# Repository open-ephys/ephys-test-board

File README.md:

# General purpose, automated electrophysiology test board

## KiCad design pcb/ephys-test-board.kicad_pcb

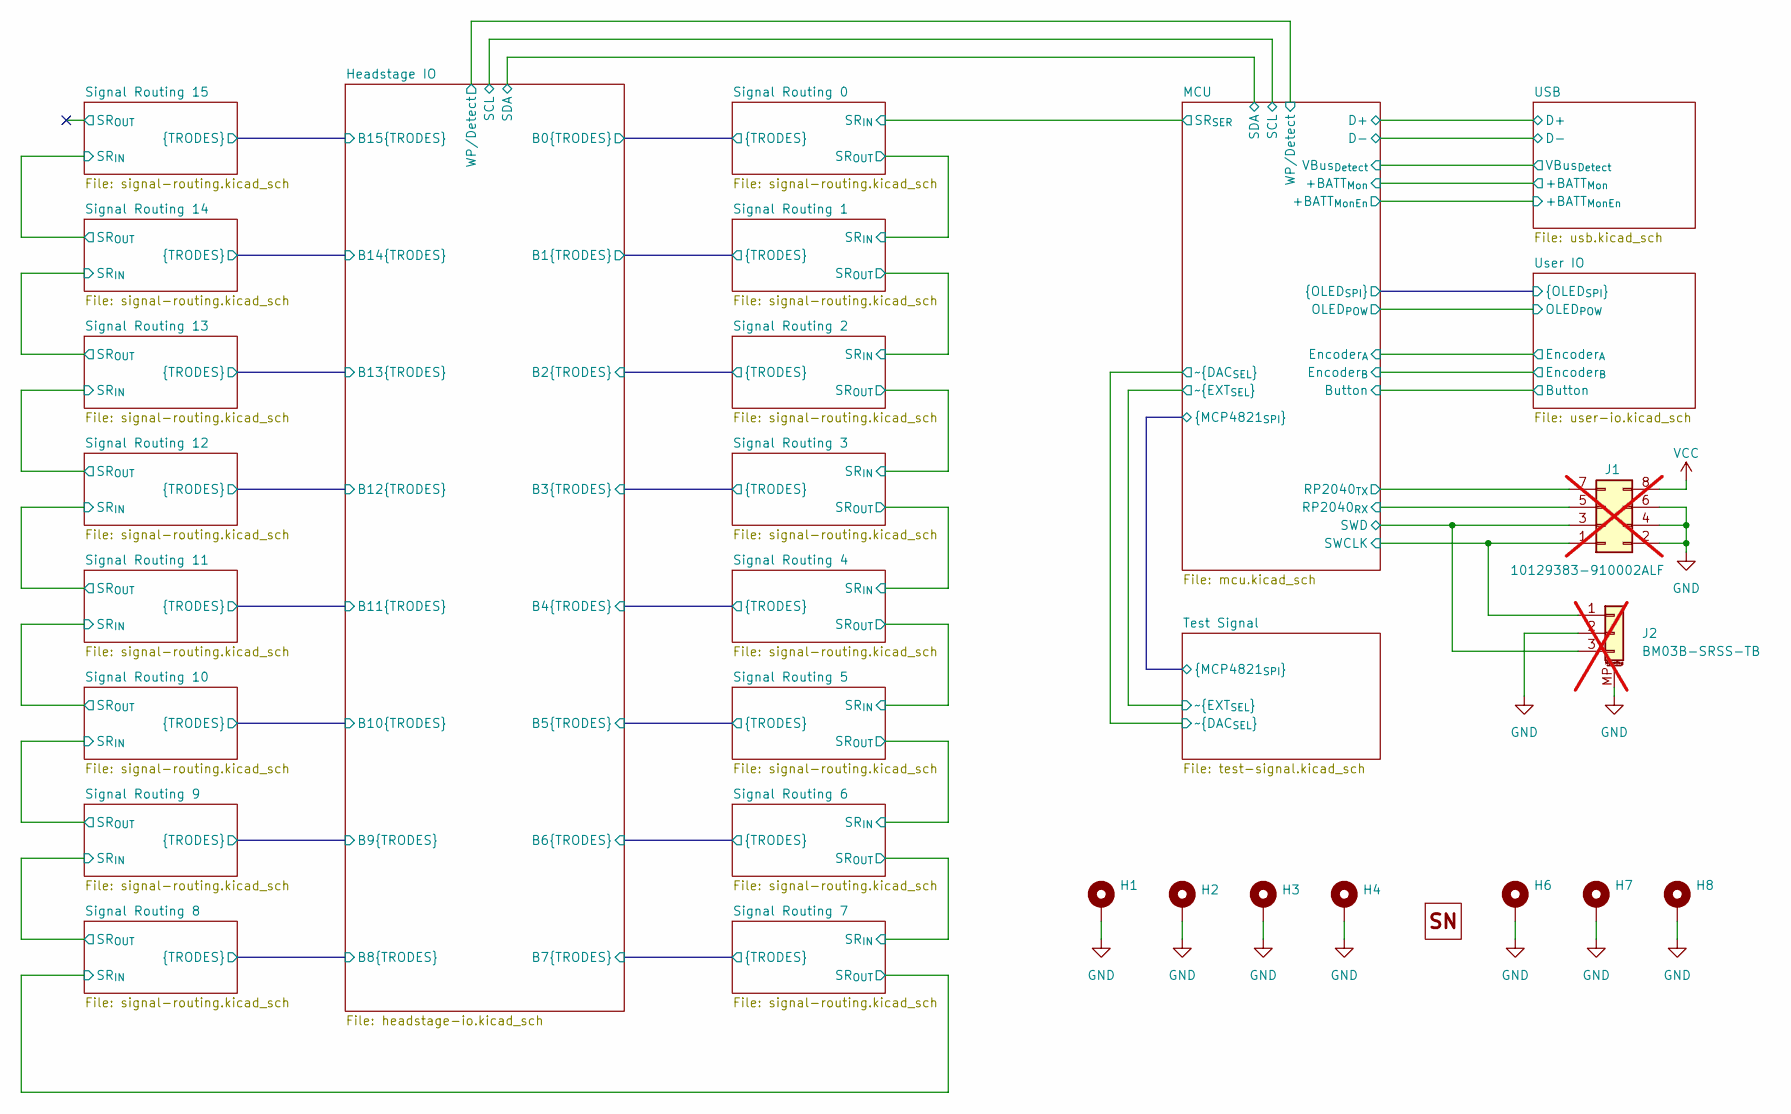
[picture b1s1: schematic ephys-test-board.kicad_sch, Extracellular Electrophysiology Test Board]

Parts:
H1, H2, H3, H4, H6, H7, H8: MountingHole_3.2mm_M3_ISO7380_Pad
H5: OEPS_SN-STICKER-8x20mm
J1: 10129383-910002ALF; PinHeader_2x04_P2.54mm_Vertical_SMD; MPN 10129383-910002ALF; not fitted
J2: BM03B-SRSS-TB; JST_SH_BM03B-SRSS-TB_1x03-1MP_P1.00mm_Vertical; MPN BM03B-SRSS-TB; not fitted

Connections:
/MCU/RP2040_{RX}: J1.5; also elsewhere on the board
/MCU/RP2040_{TX}: J1.7; also elsewhere on the board
/MCU/SWCLK: J1.1, J2.1; also elsewhere on the board
/MCU/SWD: J1.3, J2.3; also elsewhere on the board
GND: H1.1 (1_1), H2.1 (1_1), H3.1 (1_1), H4.1 (1_1), H6.1 (1_1), H7.1 (1_1), H8.1 (1_1), J1.2, J1.4, J1.6, J2.2, J2.MP (MountPin); also elsewhere on the board
VCC: J1.8; also elsewhere on the board

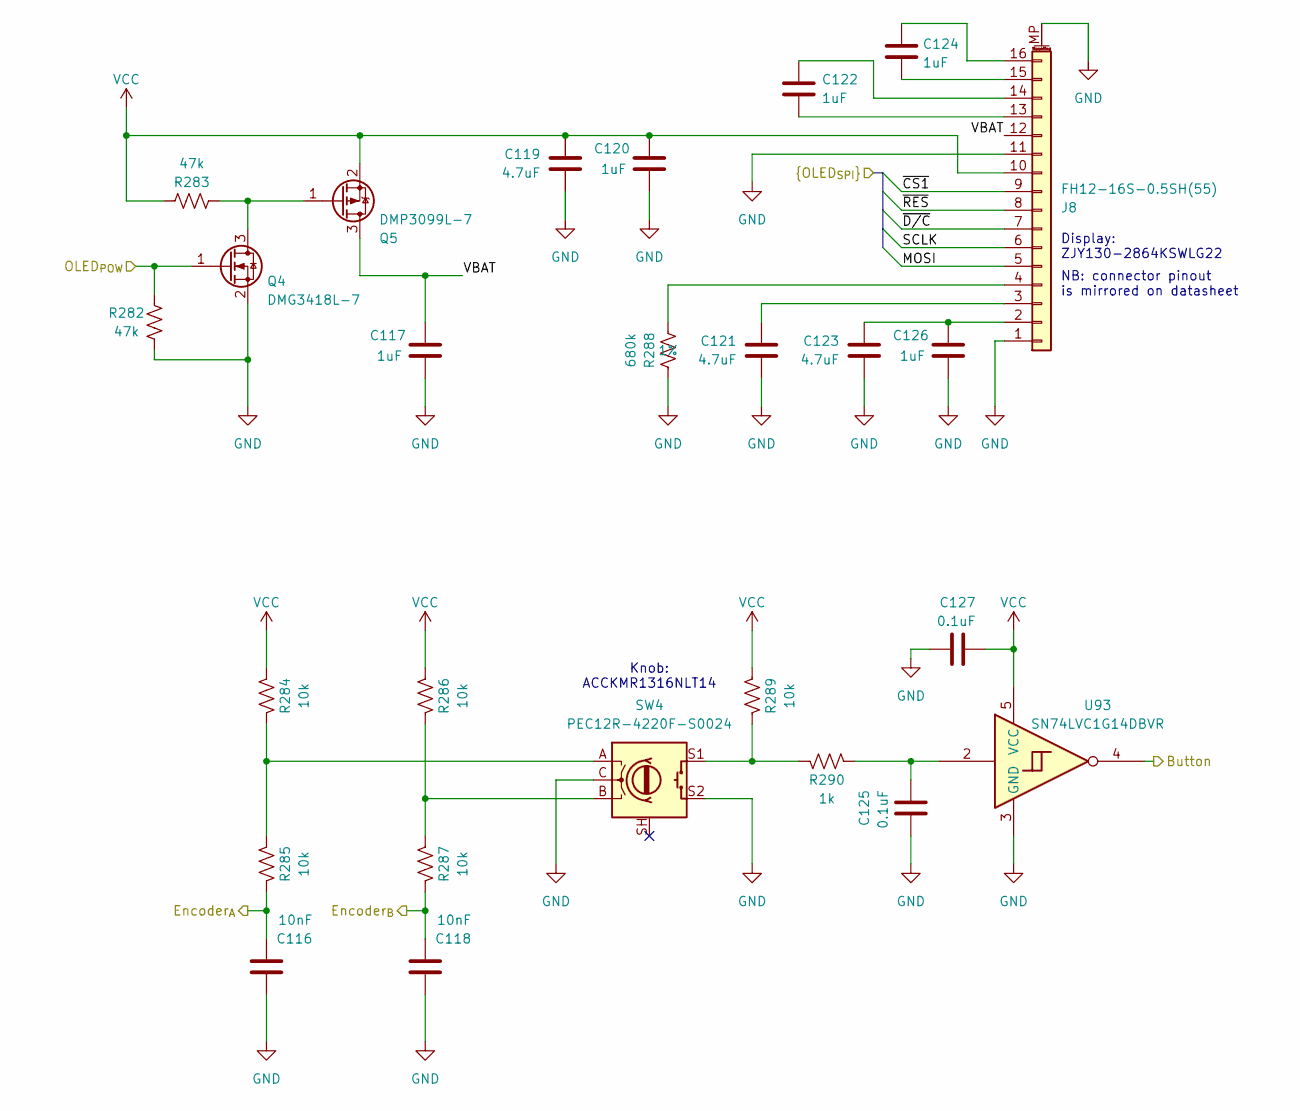
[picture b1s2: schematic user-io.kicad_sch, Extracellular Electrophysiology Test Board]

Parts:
C116, C118: 10nF; C_0402_1005Metric; Voltage 50V; MPN GRM155R71E103KA01D; LCSC C60133
C117, C120, C122, C124, C126: 1uF; C_0603_1608Metric; Voltage 16V; MPN CL10A105KA8NNNC; LCSC C5673
C119, C121, C123: 4.7uF; C_1206_3216Metric; Voltage 16V; MPN CL31B475KOHNNNE; LCSC C51205
C125, C127: 0.1uF; C_0402_1005Metric; Voltage 25V; MPN C1005X7R1E104K050BB; LCSC C105883
J8: FH12-16S-0.5SH(55); Hirose_FH12-16S-0.5SH_1x16-1MP_P0.50mm_Horizontal; MPN FH12-16S-0.5SH(55); LCSC C262665
Q4: DMG3418L-7; SOT-23; MPN DMG3418L-7; LCSC C151026
Q5: DMP3099L-7; SOT-23; MPN DMP3099L-7; LCSC C155244
R282, R283: 47k; R_0402_1005Metric; MPN ERJ-2RKF4702X; LCSC C93943
R284, R285, R286, R287, R289: 10k; R_0402_1005Metric; MPN CRCW040210K0FKED; LCSC C60490
R288: 680k; R_0402_1005Metric; Tolerance 1%; MPN RC0402FR-13680KL; LCSC C2909377
R290: 1k; R_0402_1005Metric; Tolerance 0.1%; MPN RG1005P-102-B-T5; LCSC C2073397
SW4: PEC12R-4220F-S0024; RotaryEncoder_Bourns_Vertical_PEC12R-3x17F-Sxxxx; MPN PEC12R-4220F-S0024; LCSC C18164805
U93: SN74LVC1G14DBVR; SOT-23-5; MPN SN74LVC1G14DBVR; LCSC C7835

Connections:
/MCU/Button: U93.4; also elsewhere on the board
/MCU/Encoder_{A}: C116.1, R285.2; also elsewhere on the board
/MCU/Encoder_{B}: C118.1, R287.2; also elsewhere on the board
/MCU/MOSI: J8.5; also elsewhere on the board
/MCU/OLED_{POW}: Q4.1 (G), R282.1; also elsewhere on the board
/MCU/SCLK: J8.6; also elsewhere on the board
/MCU/~CS1: J8.9; also elsewhere on the board
/MCU/~D/C: J8.7; also elsewhere on the board
/MCU/~RES: J8.8; also elsewhere on the board
/User IO/VBAT: C117.2, J8.12, Q5.3 (D)
GND: C116.2, C117.1, C118.2, C119.2, C120.1, C121.2, C123.2, C125.2, C126.1, C127.2, J8.1, J8.11, J8.MP (MountPin), Q4.2 (S), R282.2, R288.2, SW4.C, SW4.S2, U93.3 (GND); also elsewhere on the board
unnamed: C125.1, R290.2, U93.2
unnamed: C123.1, C126.2, J8.2
unnamed: C121.1, J8.3
unnamed: J8.4, R288.1
unnamed: C122.1, J8.13
unnamed: C122.2, J8.14
unnamed: C124.1, J8.15
unnamed: C124.2, J8.16
unnamed: Q4.3 (D), Q5.1 (G), R283.1
unnamed: R284.2, R285.1, SW4.A
unnamed: R286.2, R287.1, SW4.B
unnamed: R289.2, R290.1, SW4.S1
VCC: C119.1, C120.2, C127.1, J8.10, Q5.2 (S), R283.2, R284.1, R286.1, R289.1, U93.5 (VCC); also elsewhere on the board

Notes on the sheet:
Display: ZJY130-2864KSWLG22
Knob: ACCKMR1316NLT14
NB: connector pinout is mirrored on datasheet

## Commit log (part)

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2024-01-03 Initial commit
    - Add proof of concept signal path verification board
2024-01-08 Started messing around with firmware
    - Messing around with pico-sdk and thinking about how the board will operate.
    - This is just scratch code.
2024-01-29 Add results from signal-path-test board
    - The conclusion is obvious in hind-sight: attenuation must occur after
    analog switches otherwise the small noise of the signal is added to
    the attenuated signal. If attenuation occurs after the switch, this
    still occurs but the lage signal and added noise are _both_ attenuated
    and the noise from the switch is not relevant
2024-01-29 Add initial ephys test board schematic
    - Needs a display to be added
    - Needs concreate part numbers and packages
2024-05-21 Remove battery power option
    - This device needs user IO
    - Battery power means there would need to be a touch screen or wireless
    connection. Too complex.
2024-10-11 Motif is repeated
    - some components are grouped by function
    - components are roughly organized within groups
2024-11-03 Add Cris's instructions for repeating circuit motif
    - Minor edits to markdown
2024-11-08 Manual cleanup of repeated analog input array
    - There was some manual cleanup needed
    - Overall the repeated motif worked very well
2024-11-08 Added user IO and battery
    - Battery provides noise free operation
    - OLED display and rotary encoder are not that hard to use
2024-11-09 Add EEPROM support to headstage interface
    - I2C + Power
2024-11-10 More schematic improvements
    - Add pullups to i2c bus
    - Add test points
    - Ready for initial routing
2024-11-11 Start routing rev. A
2024-11-12 Routing nearly complete
    - Power switch is too tall I think
2024-11-14 Created case
    - Mill aluminum
    - Moved some components for more sensical layout for the user
    - Pending final check, should be ready for initial fab
2024-11-15 Improved manufacturability of case design
    - Quote request sent to PCBWay for this design along with the case
2024-11-15 Update pdf of schematic
    - Additionally, add spice verification of AD5683's
    ability to drive the combined capacitive and
    resistive load presented by the AC coupling
    and attenuation networks
2024-11-19 Fix MCP73831 subcircuit
    - Add decoupling capacitor on Vbat
    - Add more thermal support to layout (solid connection of ground to
    ground plane copper and addition of thermal vias)
2025-01-10 OLED firmware scratch
    - Minimal use of Adafruit graphics libaries
    - Functioned hacked to permit use with Pico SDK
    - translations.h/cpp provides unimplemented hardware translation code
    - Compliles but does nothing currently
    - This is all scratch pad for testing a possible solution for driving
    OLED
2025-01-22 Address several issues found when testing rev. A
    - Add Reset button to back panel
    - Make board smaller
    - Move battery to bottom of device
    - Replace OLED with a more reasonable choice.
    - Etc.
2025-02-06 Change power switch
    - Replace push button with rocker
    - Added some notches to outside of PCB for aligning with enclosure
    - Upgrade to KiCAD 9.0
2025-02-07 Revision B
    - Sent to fab
2025-02-09 Move SW4 closer to PCB edge
    - Also, correct its footprint to 5.8mm actuator length rather than 8.3
    which did not match its part number
2025-02-09 Fix J4 value
    - FH12-16S-0.5SH(55) instead of FH12-24S-0.5SH(55)
2025-02-28 Mirror connections on J4
    - The schematic presented on OLED datasheet was mirrored commpared to
    the connector's pin order. This fixes that.
2025-02-28 Decrease charge indication LED brightness
    - 1k current limiting resistor replaced with 4.7k
2025-03-12 Firmware work
    - Added mode seleciton capabilites
    - Started on channel selection, etc
2025-03-15 Firmware work in progress
    - Knob turns in correct direction
    - Working on incorporating waveform information into waveform generator
2025-03-18 Functional firmware
    - There are some TODOs throughout the code but but this is nearly
    feature complete
    - Spikes waveform maps to sawtooth, that needs to be changed
    - Channel cycling, module eeprom loading, knob hysteresis, and much more
    is all taken care of
2025-03-20 Firmware updates
    - Press button now cycles selection
    - Slow down quadrature PIO state machine to prevent glitching
    - Remove redundant OLED update calls
    - Code cleanup and streamlining
2025-03-20 Reduce test signal attenuation
    - From -60 dbV to -54 dbV
2025-03-20 Add SC0914(13) to Part No. field of RP2040
2025-03-20 Correct max amplitude
    - It was 250 uV but should be 2500 uV
2025-03-21 Case for revision C of PCB
    - Will require some modifications to screen area if its to be
    machinable.
2025-03-21 Add open ephys sheet to pcb design
2025-03-26 Add light pipe part to schematic.
2025-03-29 Address issues with case found during proptyping
    - Add recess for reset button
    - Add 3.5V power managment circuit and simplify on/off switch debounce
    - Increase space in bottom porition of case for thicker battery
    - Remove alignment notches from PCB -- uses features of case instead
2025-04-01 Add silkscreen design for case
    - Also, add recess for sticker on bottom of case
    - Improve case manufacturablity after testing
2025-04-07 Remove signal-path-test-board
    - It has been integrated into the main board
2025-04-07 Add license
2025-04-07 Update gerbers with latest
    - Board Rev -> Rev on silk layer
2025-04-09 Add protention diode to USB input
    - Same part that has been verified on stimjim-hv
2025-04-15 Added OEPS PN.
2025-04-16 Minor edits during BOM review
    - Remove DNP in value fields since a dedicated channel is provided for
    that information
    - Add MP pins to header symbols
    - Update BOM and PDFs
    - New gerbers to connect mount points to headers. No component position
    changes
2025-04-21 Add case assembly instructions
2025-04-21 Add missing case/README.md file
2025-07-02 Edits to firmware for rev. C
    - Added spike waveform
    - Modified EEPROM interface for new 16-vit address chip
    - Modified module detection logic
2025-07-03 Point MODULE_DETECT to the right pin
2025-07-03 Updated default frequency to 1000 Hz
2025-07-03 Increased splash time to 3 seconds
2025-07-03 Add bypass for battery protection circuit
    - Mark battery protection circuit as DNP
    - Add 0-Ohm jumper from negative battery terminal to ground
2025-07-04 Added OEPS PN to the new resistor
2025-07-04 Propagated DNP attribute to PCB
2025-07-11 Add battery measurement circuit
    - Measure battery voltage using microcontroller's ADC
2025-07-12 Add battery monitor firmware
    - Shows battery icon with discharge status
    - Linear regime will need to be tuned once I have revision D hardware
    - Shows when USB is detected
2025-07-23 Add short channel cycle mode
    - Also add all channel active step at the start of each channel cycle
    that makes synchronization easy for automatic testing
2025-08-13 Implement firmware for EEPROM layout version 1.0
    - Includes multiple maps per module
2025-08-13 Add schottky diode in series with VDD on U153
    - This diode is required to prevent C299 from forming a very
    long RC circuit with R264/5, which causes long turn on time for Q1 and
    long time period in triode regime, which causes VPP to droop, which
    causes U154 to issue reset and the circuit to power cycle when USB
    cable is unplugged.
2025-09-24 Updated BOM export settings and grouping
    Changed BOM export options to meet the requirements of the turnkey manufacturers.
2025-09-24 Added MPN and OEPSPN properties to op-amp U149
    Added manufacturer part number (MPN: TLV9061IDBVR) and OEPSPN (OEPS080179) properties to the op-amp U149.
2025-09-24 Reordered BOM export settings and added BOM.csv
2025-09-29 Use 1.25V reference voltage for electrode test signal
    - This prevents large AC component when channel switch occurs.
    - Previously the attenuator reference and nomimal electrode signals were
    both ground. Since the test signal is centered arround 1.25V, there
    the test signal is effectively a 1.25V square wave + the indented
    signal. The square waves edges were readily passed through the AC
    coupling capacitor.
2025-10-02 Added dedicated TESTREF pin on headstage interface
    - Also removed GND conenctions from 3 pins and marked as reserved
2025-10-02 Dont change DC level when scaling test signal
    - Test signal was being scaled via simple bit shift, but this scaled
    thed DC offset as well, causing jumps. Now, only the AC component is
    scaled
    - Add battery status update during channel map selection
2025-11-03 Revision E
    - Sent for fabrication and assembly
    - JLC BOM and component placements added to manufacturing folder
2026-01-06 Implmenent bipolar test signal
    - Generate internal negative rail
    - Shift DAC output by VREF/2
    - Replace analog switches with depletion mode switches to allow negative
    signals
    - DC couple electrode inputs
2026-02-25 Update firmware for Rev. F
    - Use user specified nCS line in OLED SPI controller
    - Implement new control lines for routing test signal and enableing
    battery monitor
2026-02-25 Revision G candidate
    - Fix flipped power/ground connections on U84
    - VCC is now 3.0V
    - Address issues with parasitic voltage feedthrough on FSA533
    - Completely redesign test signal analog section with much
    improved noise, THD, etc and implicit low THD input protection on the
    external input.
2026-02-26 Update case for PCB revision G
    - Add PCB mounting holes to top
    - Update tap positions drawing
    - Improve silkscreen text and alignment
2026-02-26 Fix battery voltage measurment
    - Rev. G of board operates on 3.0V instead of 3.3V which is relevant for
    ADC conversion
2026-03-04 Update BOM field visibility and sort
2026-03-04 Add PnP files
    Update ephys-test-board schematic to match the number of components in the BOM and number of lines in the PnP files.
2026-03-13 Updated OEPS PN and regenerated BOM and PnP files
2026-03-17 Rev. G production candidate
    - Finished LCSC part numbers
    - Generated final gerbers
2026-03-25 Firmware updates for rev. G
    - Added DC signal
    - Added clipping indicator
    - Moved Adafruit OLED library into its own subfolder with splash.h,
    README.md, and license.txt included to comply with their license terms
    - Added firmware version macros and display version on splash
2026-03-30 Minor BOM fix before production
    Update the 1k 0402 resistor footprint/PN across BOM and schematics.
2026-03-31 Rev. G firmware changes
    - Fix scaling of spikes.h look up tables. These are now 1:1 with
    physical units and can be scaled up or down.
    - Improve clipping icons
2026-04-03 Firmware bug fixes
    - Prevent possible dereference of timer_data by one core_1 while is
    being written by core_o
    - Enforce max amplitude scaling of 2000% and fix character buffers for
    printing this to OLED
    - Remove repeated 500 Hz entry in FREQ_LUT
2026-04-13 Improve quadrature detent detection algorithm
    - This is a simplificaiton of the overly complicated phase detection
    algorithm in previous commits. Essentially, this algorithm simply
    moves the anchor position for registering a detent along with turning,
    in the direciton of turning. This provides automatic hysteresis and
    works well in practice.
2026-05-03 Rev. G firmware fixes
    - DC waveform was continuing to apply whatever AC waveform was last
    selected
    - DC waveform display was messed up
    - Fix constants in lut that were not updated when I removed duplicate entry
    from the frequency table
